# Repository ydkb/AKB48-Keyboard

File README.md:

# AKB48-Keyboard
Atreus Keyboard 48

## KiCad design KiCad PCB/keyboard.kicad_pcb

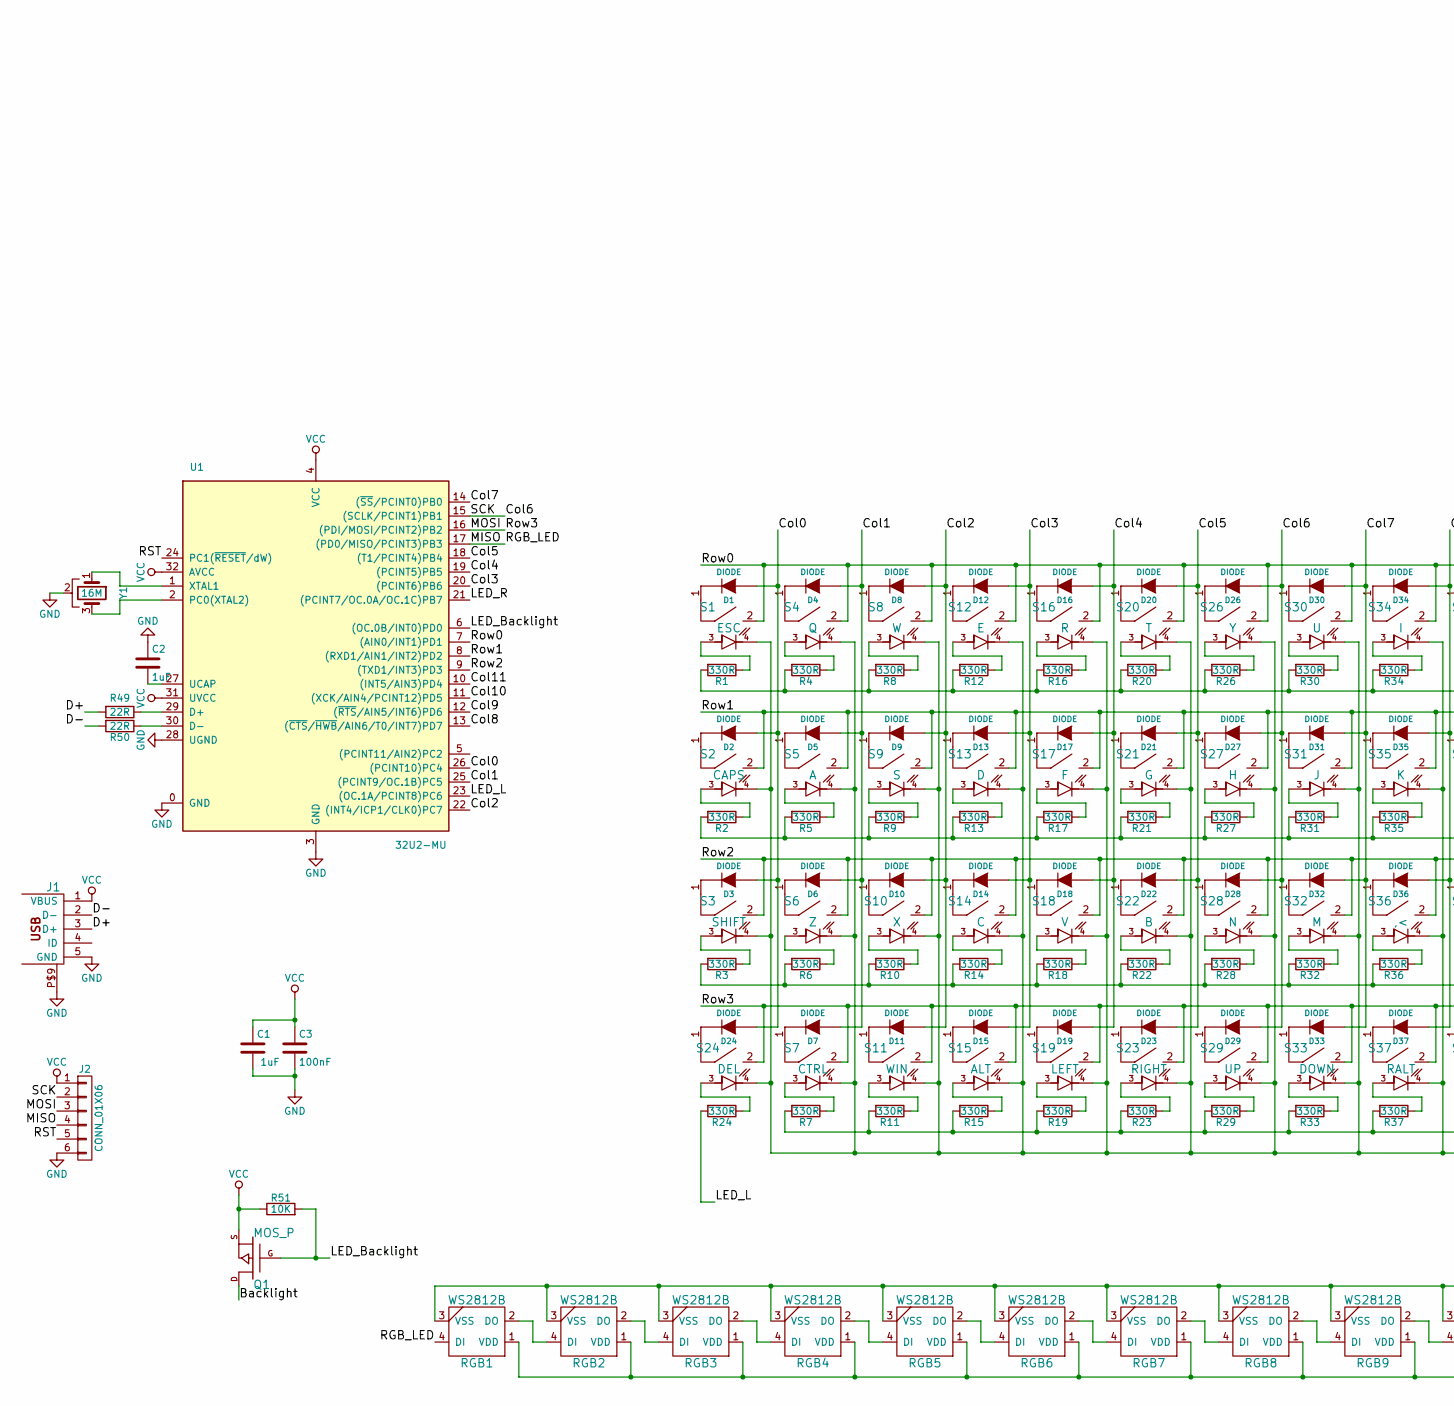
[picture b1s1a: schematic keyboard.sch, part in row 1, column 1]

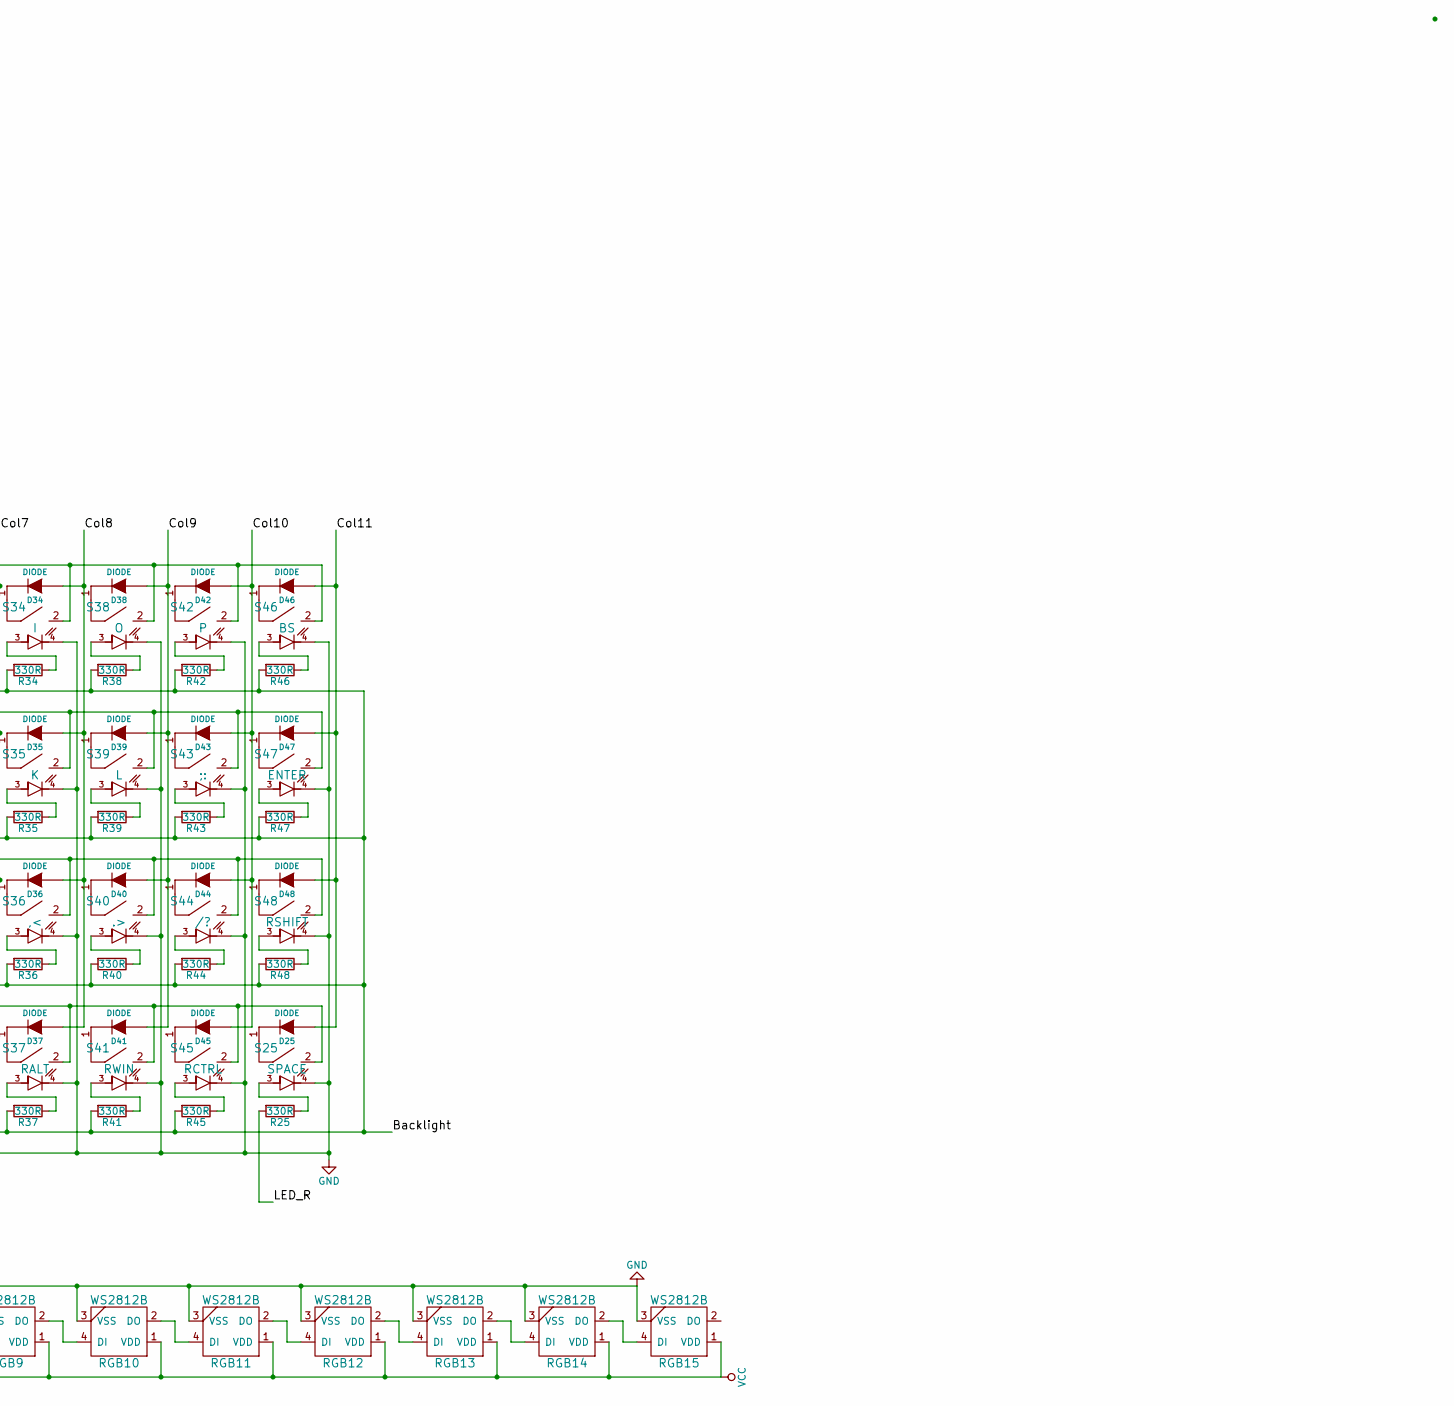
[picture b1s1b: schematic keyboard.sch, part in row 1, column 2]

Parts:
C1, C2: 1uF; C_0805
C3: 100nF; C_0805
D1, D2, D3, D4, D5, D6, D7, D8, D9, D10, D11, D12, D13, D14, D15, D16, D17, D18, D19, D20, D21, D22, D23, D24: DIODE; D_0805
D25, D26, D27, D28, D29, D30, D31, D32, D33, D34, D35, D36, D37, D38, D39, D40, D41, D42, D43, D44, D45, D46, D47, D48: DIODE; D_0805_2
J1: USB; DX_USB
J2: CONN_01X06; ISP_1x6_1.27mm
Q1: MOS_P; SOT-23
R1, R2, R3, R4, R5, R6, R7, R8, R9, R10, R11, R12, R13, R14, R15, R16, R17, R18, R19, R20, R21, R22, R23, R24: 330R; R_0805
R25, R26, R27, R28, R29, R30, R31, R32, R33, R34, R35, R36, R37, R38, R39, R40, R41, R42, R43, R44, R45, R46, R47, R48: 330R; R_0805_2
R49, R50: 22R; R_0805
R51: 10K; R_0805
RGB1, RGB2, RGB3, RGB4, RGB5, RGB6, RGB7, RGB8, RGB9, RGB10, RGB11, RGB12, RGB13, RGB14, RGB15: WS2812B
S1: ESC; MX1A_LED
S2: CAPS; MX1A_LED
S3: SHIFT; MX1A_LED
S4: Q; MX1A_LED
S5: A; MX1A_LED
S6: Z; MX1A_LED
S7: CTRL; MX1A_LED
S8: W; MX1A_LED
S9: S; MX1A_LED
S10: X; MX1A_LED
S11: WIN; MX1A_LED
S12: E; MX1A_LED
S13: D; MX1A_LED
S14: C; MX1A_LED
S15: ALT; MX1A_LED
S16: R; MX1A_LED
S17: F; MX1A_LED
S18: V; MX1A_LED
S19: LEFT; MX1A_LED
S20: T; MX1A_LED
S21: G; MX1A_LED
S22: B; MX1A_LED
S23: RIGHT; MX1A_LED
S24: DEL; MX1A_LED
S25: SPACE; MX1A_LED_AKB48R
S26: Y; MX1A_LED_AKB48R
S27: H; MX1A_LED_AKB48R
S28: N; MX1A_LED_AKB48R
S29: UP; MX1A_LED_AKB48R
S30: U; MX1A_LED_AKB48R
S31: J; MX1A_LED_AKB48R
S32: M; MX1A_LED_AKB48R
S33: DOWN; MX1A_LED_AKB48R
S34: I; MX1A_LED_AKB48R
S35: K; MX1A_LED_AKB48R
S36: ,<; MX1A_LED_AKB48R
S37: RALT; MX1A_LED_AKB48R
S38: O; MX1A_LED_AKB48R
S39: L; MX1A_LED_AKB48R
S40: .>; MX1A_LED_AKB48R
S41: RWIN; MX1A_LED_AKB48R
S42: P; MX1A_LED_AKB48R
S43: ;:; MX1A_LED_AKB48R
S44: /?; MX1A_LED_AKB48R
S45: RCTRL; MX1A_LED_AKB48R
S46: BS; MX1A_LED_AKB48R
S47: ENTER; MX1A_LED_AKB48R
S48: RSHIFT; MX1A_LED_AKB48R
U1: 32U2-MU; QFN32-Circle
Y1: 16M; CSTCE

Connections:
/Backlight: Q1.D, R1.2, R2.2, R3.2, R4.2, R5.2, R6.2, R7.2, R8.2, R9.2, R10.2, R11.2, R12.2, R13.2, R14.2, R15.2, R16.2, R17.2, R18.2, R19.2, R20.2, R21.2, R22.2, R23.2, R26.2, R27.2, R28.2, R29.2, R30.2, R31.2, R32.2, R33.2, R34.2, R35.2, R36.2, R37.2, R38.2, R39.2, R40.2, R41.2, R42.2, R43.2, R44.2, R45.2, R46.2, R47.2, R48.2
/Col0: D1.1 (A), D2.1 (A), D3.1 (A), D24.1 (A), U1.26 ((PCINT10)PC4)
/Col1: D4.1 (A), D5.1 (A), D6.1 (A), D7.1 (A), U1.25 ((PCINT9/OC.1B)PC5)
/Col2: D8.1 (A), D9.1 (A), D10.1 (A), D11.1 (A), U1.22 ((INT4/ICP1/CLK0)PC7)
/Col3: D12.1 (A), D13.1 (A), D14.1 (A), D15.1 (A), U1.20 ((PCINT6)PB6)
/Col4: D16.1 (A), D17.1 (A), D18.1 (A), D19.1 (A), U1.19 ((PCINT5)PB5)
/Col5: D20.1 (A), D21.1 (A), D22.1 (A), D23.1 (A), U1.18 ((T1/PCINT4)PB4)
/Col6: D26.1 (A), D27.1 (A), D28.1 (A), D29.1 (A), J2.2, U1.15 ((SCLK/PCINT1)PB1)
/Col7: D30.1 (A), D31.1 (A), D32.1 (A), D33.1 (A), U1.14 ((~SS~/PCINT0)PB0)
/Col8: D34.1 (A), D35.1 (A), D36.1 (A), D37.1 (A), U1.13 ((~CTS~/~HWB~/AIN6/T0/INT7)PD7)
/Col9: D38.1 (A), D39.1 (A), D40.1 (A), D41.1 (A), U1.12 ((~RTS~/AIN5/INT6)PD6)
/Col10: D42.1 (A), D43.1 (A), D44.1 (A), D45.1 (A), U1.11 ((XCK/AIN4/PCINT12)PD5)
/Col11: D25.1 (A), D46.1 (A), D47.1 (A), D48.1 (A), U1.10 ((INT5/AIN3)PD4)
/D+: J1.3 (D+), R49.2
/D-: J1.2 (D-), R50.2
/LED_Backlight: Q1.G, R51.2, U1.6 ((OC.0B/INT0)PD0)
/LED_L: R24.2, U1.23 ((OC.1A/PCINT8)PC6)
/LED_R: R25.2, U1.21 ((PCINT7/OC.0A/OC.1C)PB7)
/MISO: J2.4, RGB1.4 (DI), U1.17 ((PD0/MISO/PCINT3)PB3)
/MOSI: J2.3, S7.2, S11.2, S15.2, S19.2, S23.2, S24.2, S25.2, S29.2, S33.2, S37.2, S41.2, S45.2, U1.16 ((PDI/MOSI/PCINT2)PB2)
/RST: J2.5, U1.24 (PC1(~RESET~/dW))
/Row0: S1.2, S4.2, S8.2, S12.2, S16.2, S20.2, S26.2, S30.2, S34.2, S38.2, S42.2, S46.2, U1.7 ((AIN0/INT1)PD1)
/Row1: S2.2, S5.2, S9.2, S13.2, S17.2, S21.2, S27.2, S31.2, S35.2, S39.2, S43.2, S47.2, U1.8 ((RXD1/AIN1/INT2)PD2)
/Row2: S3.2, S6.2, S10.2, S14.2, S18.2, S22.2, S28.2, S32.2, S36.2, S40.2, S44.2, S48.2, U1.9 ((TXD1/INT3)PD3)
GND: C1.2, C2.1, C3.2, J1.5 (GND), J1.P$9, J2.6, RGB1.3 (VSS), RGB2.3 (VSS), RGB3.3 (VSS), RGB4.3 (VSS), RGB5.3 (VSS), RGB6.3 (VSS), RGB7.3 (VSS), RGB8.3 (VSS), RGB9.3 (VSS), RGB10.3 (VSS), RGB11.3 (VSS), RGB12.3 (VSS), RGB13.3 (VSS), RGB14.3 (VSS), RGB15.3 (VSS), S1.4, S2.4, S3.4, S4.4, S5.4, S6.4, S7.4, S8.4, S9.4, S10.4, S11.4, S12.4, S13.4, S14.4, S15.4, S16.4, S17.4, S18.4, S19.4, S20.4, S21.4, S22.4, S23.4, S24.4, S25.4, S26.4, S27.4, S28.4, S29.4, S30.4, S31.4, S32.4, S33.4, S34.4, S35.4, S36.4, S37.4, S38.4, S39.4, S40.4, S41.4, S42.4, S43.4, S44.4, S45.4, S46.4, S47.4, S48.4, U1.0 (GND), U1.3 (GND), U1.28 (UGND), Y1.2
unnamed: C2.2, U1.27 (UCAP)
unnamed: D1.2 (K), S1.1
unnamed: D2.2 (K), S2.1
unnamed: D3.2 (K), S3.1
unnamed: D4.2 (K), S4.1
unnamed: D5.2 (K), S5.1
unnamed: D6.2 (K), S6.1
unnamed: D7.2 (K), S7.1
unnamed: D8.2 (K), S8.1
unnamed: D9.2 (K), S9.1
unnamed: D10.2 (K), S10.1
unnamed: D11.2 (K), S11.1
unnamed: D12.2 (K), S12.1
unnamed: D13.2 (K), S13.1
unnamed: D14.2 (K), S14.1
unnamed: D15.2 (K), S15.1
unnamed: D16.2 (K), S16.1
unnamed: D17.2 (K), S17.1
unnamed: D18.2 (K), S18.1
unnamed: D19.2 (K), S19.1
unnamed: D20.2 (K), S20.1
unnamed: D21.2 (K), S21.1
unnamed: D22.2 (K), S22.1
unnamed: D23.2 (K), S23.1
unnamed: D24.2 (K), S24.1
unnamed: D25.2 (K), S25.1
unnamed: D26.2 (K), S26.1
unnamed: D27.2 (K), S27.1
unnamed: D28.2 (K), S28.1
unnamed: D29.2 (K), S29.1
unnamed: D30.2 (K), S30.1
unnamed: D31.2 (K), S31.1
unnamed: D32.2 (K), S32.1
unnamed: D33.2 (K), S33.1
unnamed: D34.2 (K), S34.1
unnamed: D35.2 (K), S35.1
unnamed: D36.2 (K), S36.1
unnamed: D37.2 (K), S37.1
unnamed: D38.2 (K), S38.1
unnamed: D39.2 (K), S39.1
unnamed: D40.2 (K), S40.1
unnamed: D41.2 (K), S41.1
unnamed: D42.2 (K), S42.1
unnamed: D43.2 (K), S43.1
unnamed: D44.2 (K), S44.1
unnamed: D45.2 (K), S45.1
unnamed: D46.2 (K), S46.1
unnamed: D47.2 (K), S47.1
unnamed: D48.2 (K), S48.1
unnamed: R1.1, S1.3
unnamed: R2.1, S2.3
unnamed: R3.1, S3.3
unnamed: R4.1, S4.3
unnamed: R5.1, S5.3
unnamed: R6.1, S6.3
unnamed: R7.1, S7.3
unnamed: R8.1, S8.3
unnamed: R9.1, S9.3
unnamed: R10.1, S10.3
unnamed: R11.1, S11.3
unnamed: R12.1, S12.3
unnamed: R13.1, S13.3
unnamed: R14.1, S14.3
unnamed: R15.1, S15.3
unnamed: R16.1, S16.3
unnamed: R17.1, S17.3
unnamed: R18.1, S18.3
unnamed: R19.1, S19.3
unnamed: R20.1, S20.3
unnamed: R21.1, S21.3
unnamed: R22.1, S22.3
unnamed: R23.1, S23.3
unnamed: R24.1, S24.3
unnamed: R25.1, S25.3
unnamed: R26.1, S26.3
unnamed: R27.1, S27.3
unnamed: R28.1, S28.3
unnamed: R29.1, S29.3
unnamed: R30.1, S30.3
unnamed: R31.1, S31.3
unnamed: R32.1, S32.3
unnamed: R33.1, S33.3
unnamed: R34.1, S34.3
unnamed: R35.1, S35.3
unnamed: R36.1, S36.3
unnamed: R37.1, S37.3
unnamed: R38.1, S38.3
unnamed: R39.1, S39.3
unnamed: R40.1, S40.3
unnamed: R41.1, S41.3
unnamed: R42.1, S42.3
unnamed: R43.1, S43.3
unnamed: R44.1, S44.3
unnamed: R45.1, S45.3
unnamed: R46.1, S46.3
unnamed: R47.1, S47.3
unnamed: R48.1, S48.3
unnamed: R49.1, U1.29 (D+)
unnamed: R50.1, U1.30 (D-)
unnamed: RGB1.2 (DO), RGB2.4 (DI)
unnamed: RGB2.2 (DO), RGB3.4 (DI)
unnamed: RGB3.2 (DO), RGB4.4 (DI)
unnamed: RGB4.2 (DO), RGB5.4 (DI)
unnamed: RGB5.2 (DO), RGB6.4 (DI)
unnamed: RGB6.2 (DO), RGB7.4 (DI)
unnamed: RGB7.2 (DO), RGB8.4 (DI)
unnamed: RGB8.2 (DO), RGB9.4 (DI)
unnamed: RGB10.2 (DO), RGB11.4 (DI)
unnamed: RGB9.2 (DO), RGB10.4 (DI)
unnamed: RGB11.2 (DO), RGB12.4 (DI)
unnamed: RGB12.2 (DO), RGB13.4 (DI)
unnamed: RGB13.2 (DO), RGB14.4 (DI)
unnamed: RGB14.2 (DO), RGB15.4 (DI)
unnamed: U1.1 (XTAL1), Y1.1
unnamed: U1.2 (PC0(XTAL2)), Y1.3
VCC: C1.1, C3.1, J1.1 (VBUS), J2.1, Q1.S, R51.1, RGB1.1 (VDD), RGB2.1 (VDD), RGB3.1 (VDD), RGB4.1 (VDD), RGB5.1 (VDD), RGB6.1 (VDD), RGB7.1 (VDD), RGB8.1 (VDD), RGB9.1 (VDD), RGB10.1 (VDD), RGB11.1 (VDD), RGB12.1 (VDD), RGB13.1 (VDD), RGB14.1 (VDD), RGB15.1 (VDD), U1.4 (VCC), U1.31 (UVCC), U1.32 (AVCC)

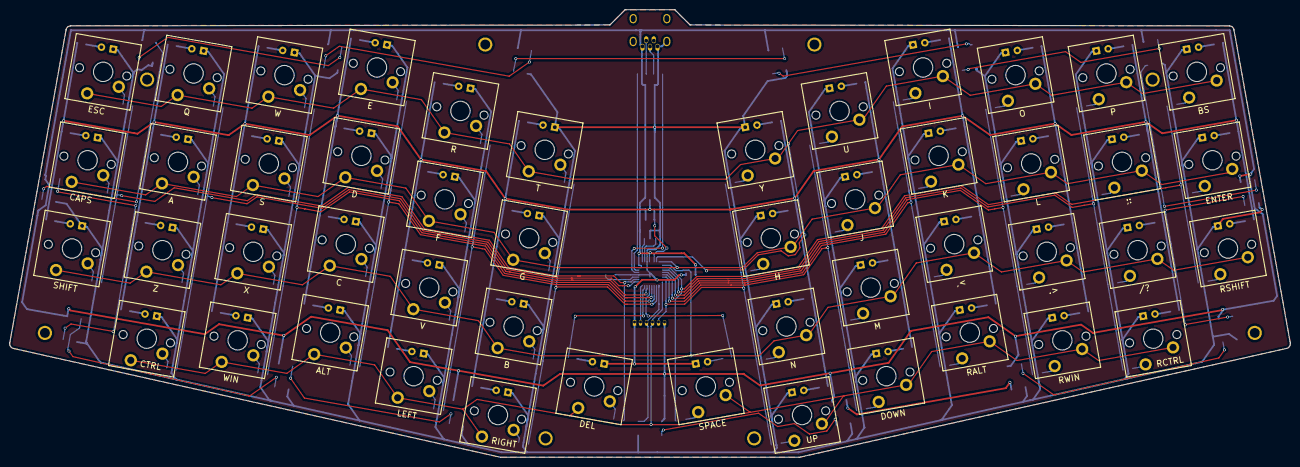
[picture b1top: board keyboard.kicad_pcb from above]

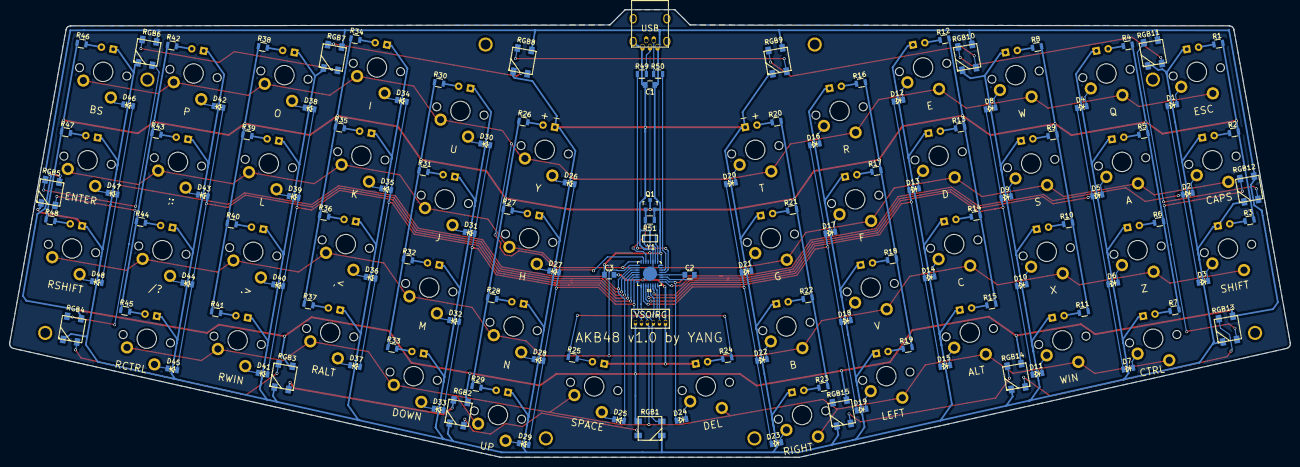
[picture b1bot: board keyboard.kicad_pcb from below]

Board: 2 copper layers, 271.0 x 94.7 mm, 170 parts (121 on the bottom side), 141 nets.

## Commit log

2021-02-13 akb48 dxf and PCB files
